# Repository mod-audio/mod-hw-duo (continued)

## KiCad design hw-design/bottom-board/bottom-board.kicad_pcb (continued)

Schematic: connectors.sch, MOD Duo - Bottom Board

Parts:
C55, C57: 100nF; C_0603_1608Metric; MPN C1608X7R1E104K080AA
C56: 10uF; CP_Elec_5x5.3; MPN UWX1E100MCL1GB
J1, J2, J3, J4, J5: JACK_TRS_6PINS; Jack_3.5mm_Neutrik_NMJ6HCD2_Horizontal; MPN NMJ6HCD2
J6: RJ45_LEDS; RJ45_Amphenol_RJHSE538X; MPN RJHSE-5381
P5: BARREL_JACK; BarrelJack_Horizontal; MPN PJ-002AH
P6: HMI_POWER; B2B-XH-A; MPN B2B-XH-A(LF)(SN)
P8: HMI_DATA; Pin_Header_Straight_2x10_Shrouded; MPN SBH11-PBPC-D10-ST-BK
P9: SERIAL_DEBUG; PinHeader_1x03_P2.54mm_Vertical
R72, R73: 100R; R_0603_1608Metric; MPN RMCF0603JT100R
R76, R77: 330R; R_0603_1608Metric; MPN RMCF0603JT330R

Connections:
+12V: C56.1, C57.1, J6.4, J6.5, P6.2; also elsewhere on the board
CLI_UART_RX: P9.2, R73.2; also elsewhere on the board
CLI_UART_TX: P9.1, R72.2; also elsewhere on the board
GNDA: C55.2, C56.2, C57.2, J1.R, J1.S, J1.TN, J2.R, J2.S, J2.TN, J3.S, J4.S, J5.S, J6.7, J6.8, J6.9, J6.11, P5.2, P5.3, P6.1, P8.2, P8.5, P8.11, P8.12, P9.3; also elsewhere on the board
HMI_ISP_ENABLE: P8.14; also elsewhere on the board
HMI_RESET: P8.16; also elsewhere on the board
HMI_RFU_01(RX): P8.1; also elsewhere on the board
HMI_RFU_02(TX): P8.3; also elsewhere on the board
HMI_SPI0_CLK: P8.8; also elsewhere on the board
HMI_SPI0_CS0: P8.10; also elsewhere on the board
HMI_SPI0_MISO: P8.4; also elsewhere on the board
HMI_SPI0_MOSI: P8.6; also elsewhere on the board
HMI_UART_RX: P8.20; also elsewhere on the board
HMI_UART_TX: P8.18; also elsewhere on the board
HP_LEFT: J5.T; also elsewhere on the board
HP_RIGHT: J5.R; also elsewhere on the board
LEFT_AUDIO_INPUT: J1.T; also elsewhere on the board
LEFT_AUDIO_OUTPUT_RING: J3.R; also elsewhere on the board
LEFT_AUDIO_OUTPUT_TIP: J3.T; also elsewhere on the board
unnamed: J6.10, R77.1
unnamed: J6.12, R76.1
unnamed: P8.7, R72.1
unnamed: P8.9, R73.1
PM_LEDS_OE: P8.15; also elsewhere on the board
POWER_BUTTON: P8.13; also elsewhere on the board
POWER_INPUT: C55.1, P5.1; also elsewhere on the board
RIGHT_AUDIO_INPUT: J2.T; also elsewhere on the board
RIGHT_AUDIO_OUTPUT_RING: J4.R; also elsewhere on the board
RIGHT_AUDIO_OUTPUT_TIP: J4.T; also elsewhere on the board
RS485_RX+: J6.3; also elsewhere on the board
RS485_RX-: J6.6; also elsewhere on the board
RS485_RX_LED: R76.2; also elsewhere on the board
RS485_TX+: J6.1; also elsewhere on the board
RS485_TX-: J6.2; also elsewhere on the board
RS485_TX_LED: R77.2; also elsewhere on the board
TWI4_SCL: P8.17; also elsewhere on the board
TWI4_SDA: P8.19; also elsewhere on the board

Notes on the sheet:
POWER
AUDIO
CONTROL CHAIN
HMI

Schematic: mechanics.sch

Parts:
FID1, FID2, FID3: FIDUCIAL; fiducial_in-circuit
H1, H2, H3, H4, H5: HOLE; Hole_3.5mm

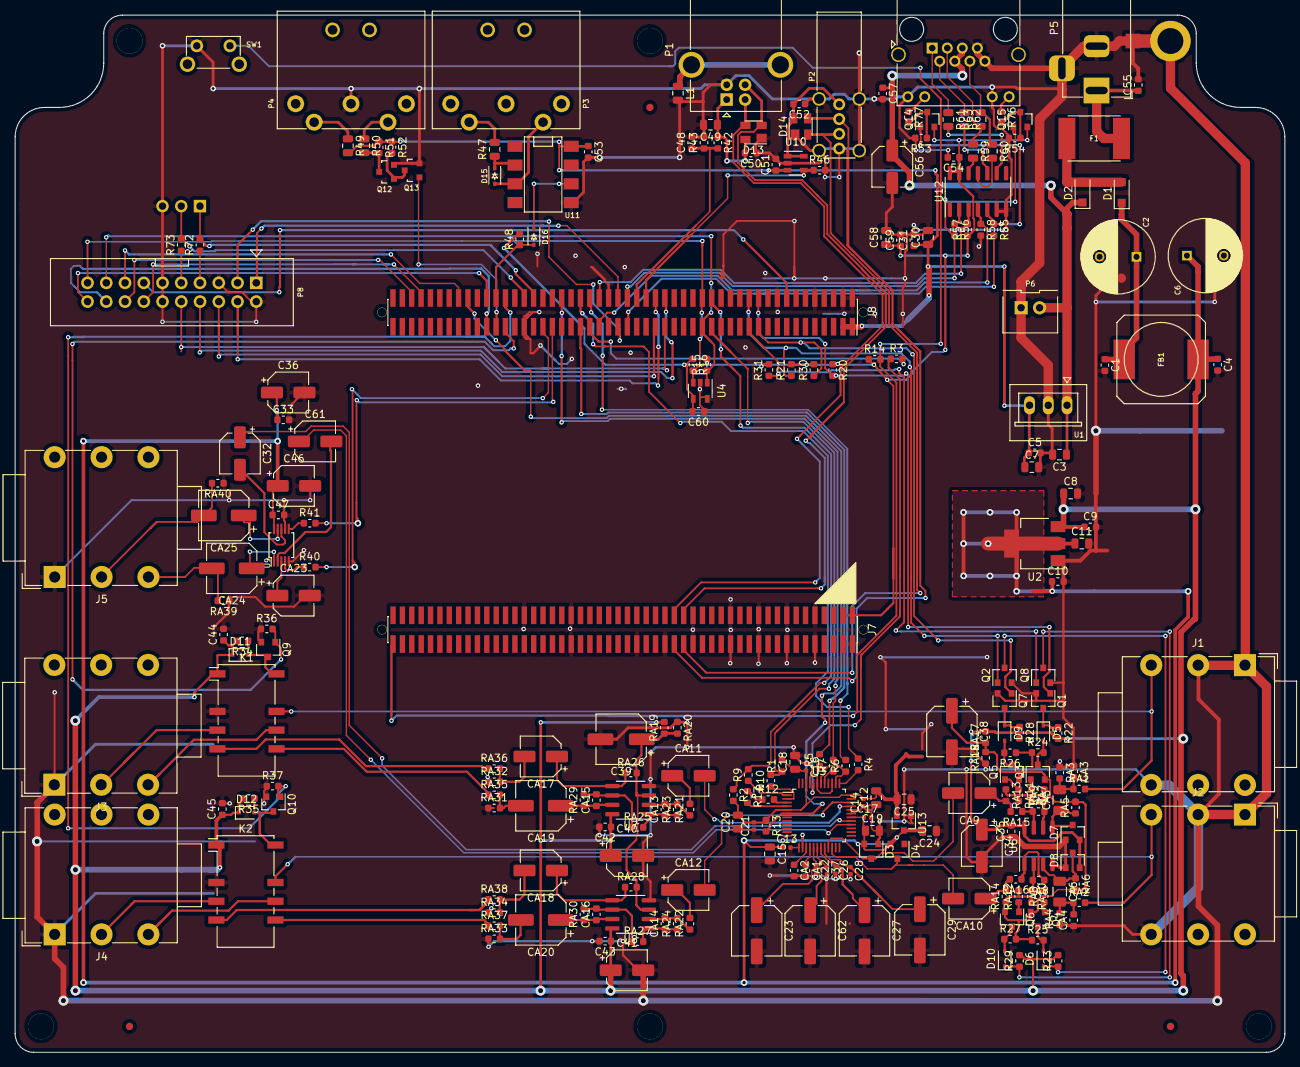
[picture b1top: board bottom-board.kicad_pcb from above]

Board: 2 copper layers, 172.0 x 140.5 mm, 255 parts (1 on the bottom side), 166 nets.

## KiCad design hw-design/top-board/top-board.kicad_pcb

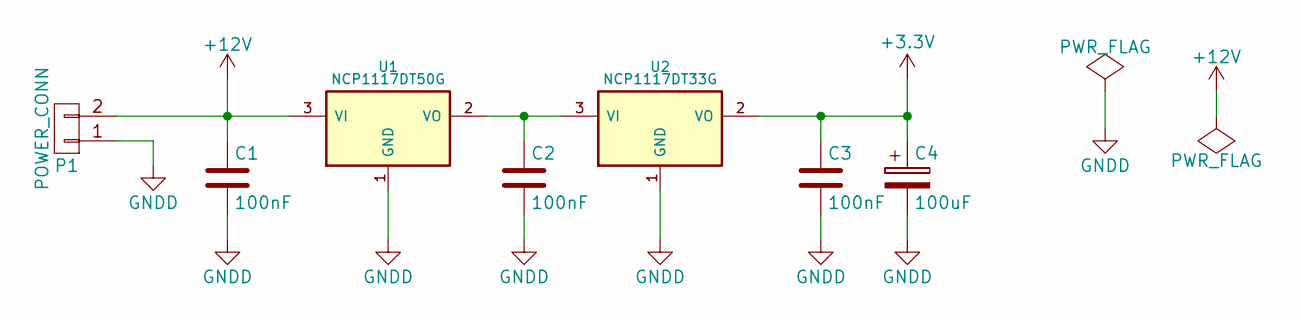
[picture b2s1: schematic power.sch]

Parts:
C1, C2, C3: 100nF; C_0603; MPN C1608X7R1E104K080AA
C4: 100uF; c_elec_6.3x5.3; MPN UWX1C101MCL1GB
P1: POWER_CONN; S2B-XH-A; MPN S2B-XH-A(LF)(SN)
U1: NCP1117DT50G; DPAK-2; MPN NCP1117DT50G
U2: NCP1117DT33G; DPAK-2; MPN NCP1117DT33G

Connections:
+3V3: C3.1, C4.1, U2.2 (VO); also elsewhere on the board
+12V: C1.1, P1.2, U1.3 (VI); also elsewhere on the board
GNDD: C1.2, C2.2, C3.2, C4.2, P1.1, U1.1 (GND), U2.1 (GND); also elsewhere on the board
unnamed: C2.1, U1.2 (VO), U2.3 (VI)

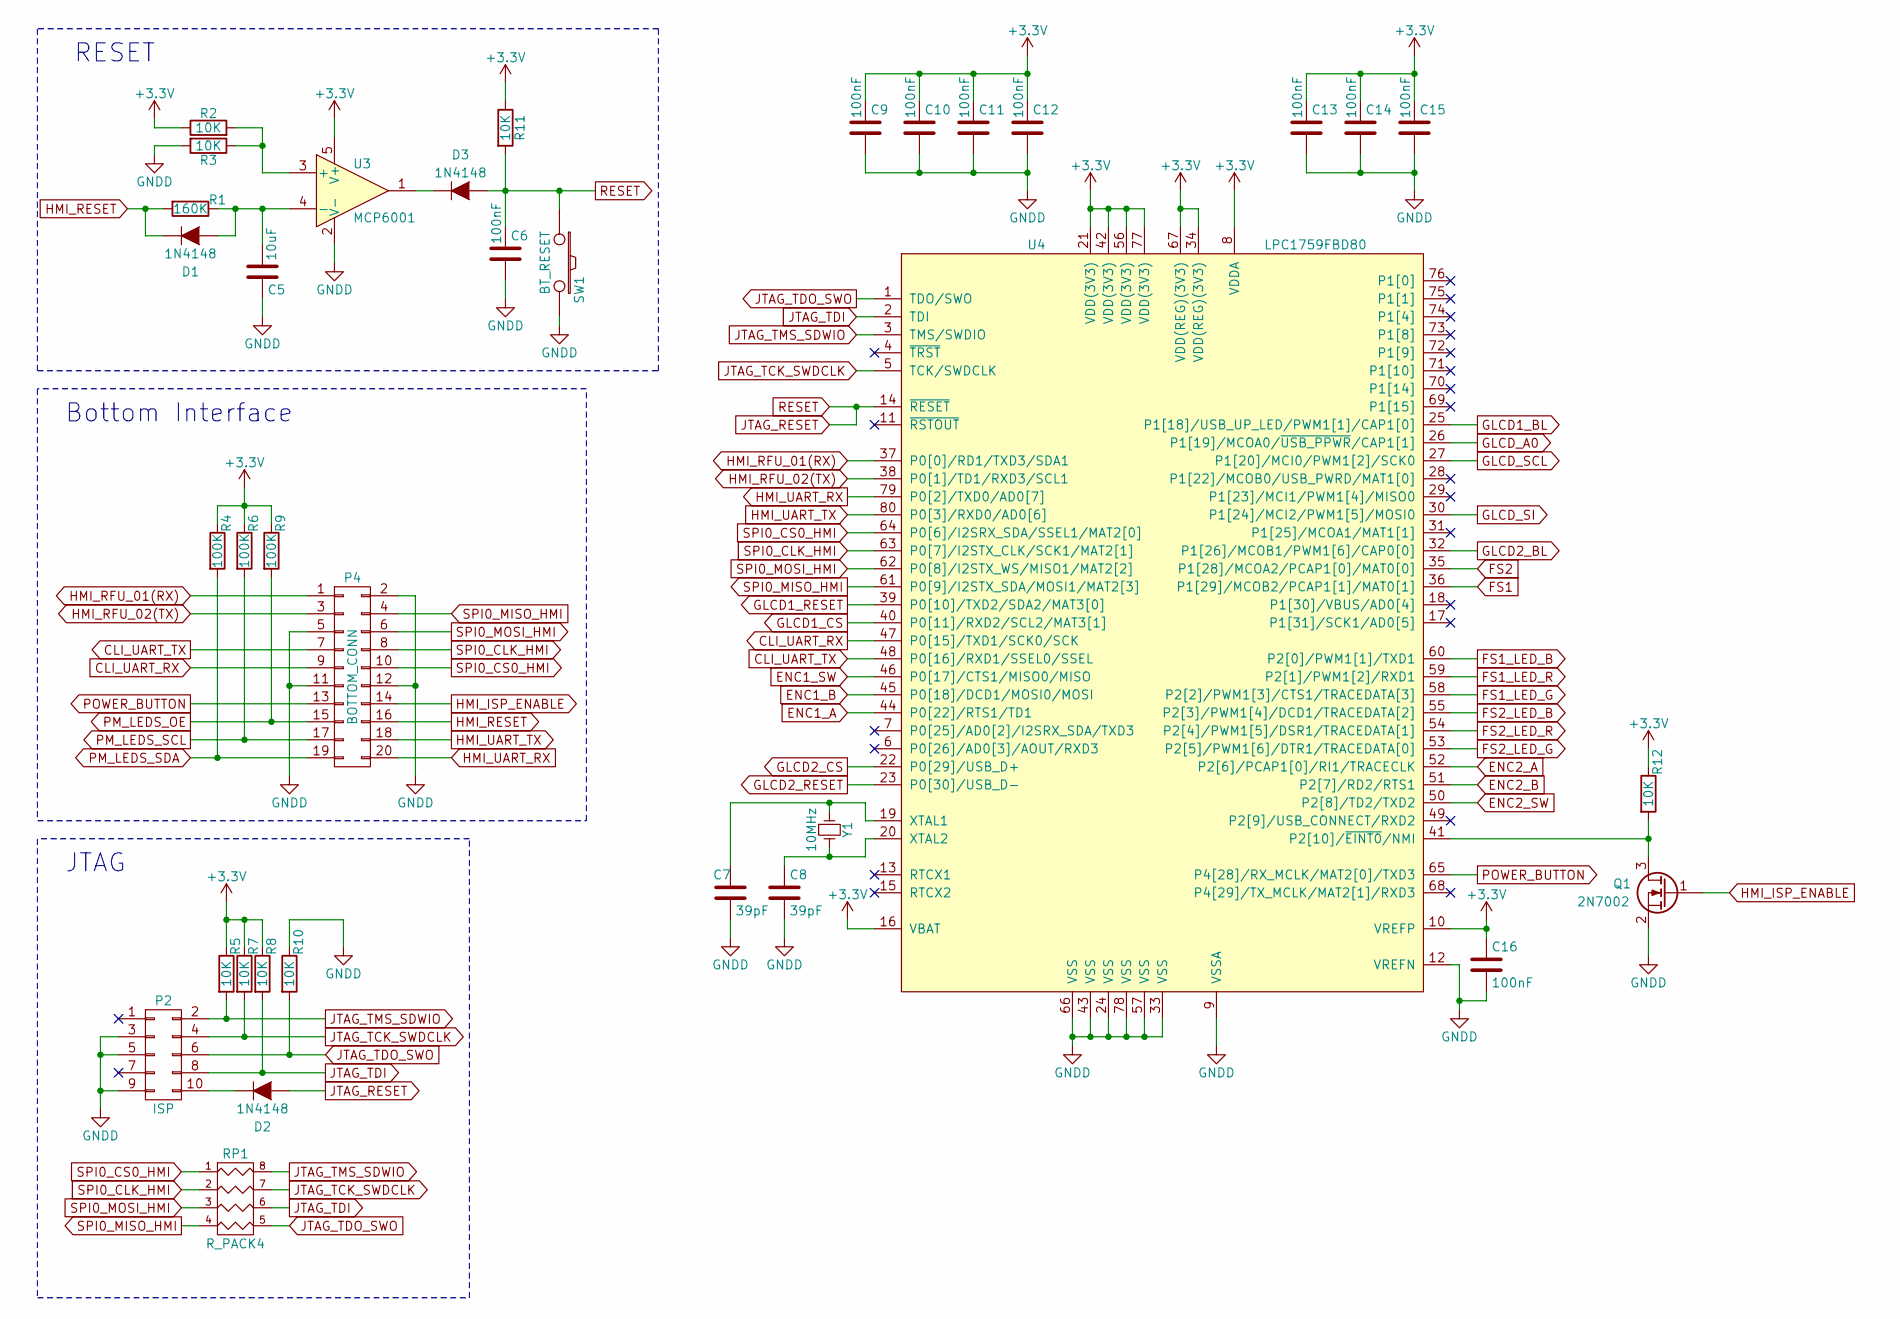
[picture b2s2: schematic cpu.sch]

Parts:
C5: 10uF; C_0805; MPN GRM219R61E106KA12D
C6, C9, C10, C11, C12, C13, C14, C15, C16: 100nF; C_0603; MPN C1608X7R1E104K080AA
C7, C8: 39pF; C_0603; MPN C1608C0G1H390J080AA
D1, D2, D3: 1N4148; SOD-323; MPN 1N4148WX-TP
P2: ISP; Pin_Header_Straight_2x05_Pitch1.27mm
P4: BOTTOM_CONN; Pin_Header_Angled_2x10; MPN 68021-220HLF
Q1: 2N7002; SOT-23; MPN 2N7002P,215
R1: 160K; R_0603; MPN RMCF0603JT160K
R2, R3, R5, R7, R8, R10, R11, R12: 10K; R_0603; MPN RMCF0603JT10K0
R4, R6, R9: 100K; R_0603; MPN RMCF0603JT100K
RP1: R_PACK4; R_Array_Concave_4x0402
SW1: BT_RESET; SW_SPST_FSMSM; MPN FSMSM
U3: MCP6001; SOT-23-5; MPN MCP6001T-I/OT
U4: LPC1759FBD80; LQFP-80_12x12mm_Pitch0.5mm; MPN LPC1759FBD80,551
Y1: 10MHz; Crystal_HC49-SD_SMD; MPN FOXSDLF/100-20

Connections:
+3V3: C9.1, C10.1, C11.1, C12.1, C13.1, C14.1, C15.1, C16.1, R2.1, R4.1, R5.1, R6.1, R7.1, R8.1, R9.1, R11.1, R12.1, U3.5 (V+), U4.8 (VDDA), U4.10 (VREFP), U4.16 (VBAT), U4.21 (VDD(3V3)), U4.34 (VDD(REG)(3V3)), U4.42 (VDD(3V3)), U4.56 (VDD(3V3)), U4.67 (VDD(REG)(3V3)), U4.77 (VDD(3V3)); also elsewhere on the board
CLI_UART_RX: P4.9, U4.47 (P0[15]/TXD1/SCK0/SCK)
CLI_UART_TX: P4.7, U4.48 (P0[16]/RXD1/SSEL0/SSEL)
ENC1_A: U4.44 (P0[22]/RTS1/TD1); also elsewhere on the board
ENC1_B: U4.45 (P0[18]/DCD1/MOSI0/MOSI); also elsewhere on the board
ENC1_SW: U4.46 (P0[17]/CTS1/MISO0/MISO); also elsewhere on the board
ENC2_A: U4.52 (P2[6]/PCAP1[0]/RI1/TRACECLK); also elsewhere on the board
ENC2_B: U4.51 (P2[7]/RD2/RTS1); also elsewhere on the board
ENC2_SW: U4.50 (P2[8]/TD2/TXD2); also elsewhere on the board
FS1: U4.36 (P1[29]/MCOB2/PCAP1[1]/MAT0[1]); also elsewhere on the board
FS1_LED_B: U4.60 (P2[0]/PWM1[1]/TXD1); also elsewhere on the board
FS1_LED_G: U4.58 (P2[2]/PWM1[3]/CTS1/TRACEDATA[3]); also elsewhere on the board
FS1_LED_R: U4.59 (P2[1]/PWM1[2]/RXD1); also elsewhere on the board
FS2: U4.35 (P1[28]/MCOA2/PCAP1[0]/MAT0[0]); also elsewhere on the board
FS2_LED_B: U4.55 (P2[3]/PWM1[4]/DCD1/TRACEDATA[2]); also elsewhere on the board
FS2_LED_G: U4.53 (P2[5]/PWM1[6]/DTR1/TRACEDATA[0]); also elsewhere on the board
FS2_LED_R: U4.54 (P2[4]/PWM1[5]/DSR1/TRACEDATA[1]); also elsewhere on the board
GLCD1_BL: U4.25 (P1[18]/USB_UP_LED/PWM1[1]/CAP1[0]); also elsewhere on the board
GLCD1_CS: U4.40 (P0[11]/RXD2/SCL2/MAT3[1]); also elsewhere on the board
GLCD1_RESET: U4.39 (P0[10]/TXD2/SDA2/MAT3[0]); also elsewhere on the board
GLCD2_BL: U4.32 (P1[26]/MCOB1/PWM1[6]/CAP0[0]); also elsewhere on the board
GLCD2_CS: U4.22 (P0[29]/USB_D+); also elsewhere on the board
GLCD2_RESET: U4.23 (P0[30]/USB_D-); also elsewhere on the board
GLCD_A0: U4.26 (P1[19]/MCOA0/~USB_PPWR~/CAP1[1]); also elsewhere on the board
GLCD_SCL: U4.27 (P1[20]/MCI0/PWM1[2]/SCK0); also elsewhere on the board
GLCD_SI: U4.30 (P1[24]/MCI2/PWM1[5]/MOSI0); also elsewhere on the board
GNDD: C5.1, C6.2, C7.2, C8.2, C9.2, C10.2, C11.2, C12.2, C13.2, C14.2, C15.2, C16.2, P2.3, P2.5, P2.9, P4.2, P4.5, P4.11, P4.12, Q1.2 (S), R3.2, R10.1, SW1.2, U3.2 (V-), U4.9 (VSSA), U4.12 (VREFN), U4.24 (VSS), U4.33 (VSS), U4.43 (VSS), U4.57 (VSS), U4.66 (VSS), U4.78 (VSS); also elsewhere on the board
HMI_ISP_ENABLE: P4.14, Q1.1 (G)
HMI_RESET: D1.1 (K), P4.16, R1.2
HMI_RFU_01(RX): P4.1, U4.37 (P0[0]/RD1/TXD3/SDA1)
HMI_RFU_02(TX): P4.3, U4.38 (P0[1]/TD1/RXD3/SCL1)
HMI_UART_RX: P4.20, U4.79 (P0[2]/TXD0/AD0[7])
HMI_UART_TX: P4.18, U4.80 (P0[3]/RXD0/AD0[6])
JTAG_RESET: C6.1, D2.2 (A), D3.2 (A), R11.2, SW1.1, U4.14 (~RESET~)
JTAG_TCK_SWDCLK: P2.4, R7.2, RP1.7 (R2), U4.5 (TCK/SWDCLK)
JTAG_TDI: P2.8, R8.2, RP1.6 (R3), U4.2 (TDI)
JTAG_TDO_SWO: P2.6, R10.2, RP1.5 (R4), U4.1 (TDO/SWO)
JTAG_TMS_SDWIO: P2.2, R5.2, RP1.8 (R1), U4.3 (TMS/SWDIO)
unnamed: C5.2, D1.2 (A), R1.1, U3.4 (-)
unnamed: C7.1, U4.19 (XTAL1), Y1.1
unnamed: C8.1, U4.20 (XTAL2), Y1.2
unnamed: D2.1 (K), P2.10
unnamed: D3.1 (K), U3.1
unnamed: Q1.3 (D), R12.2, U4.41 (P2[10]/~EINT0~/NMI)
unnamed: R2.2, R3.1, U3.3 (+)
PM_LEDS_OE: P4.15, R9.2; also elsewhere on the board
PM_LEDS_SCL: P4.17, R6.2; also elsewhere on the board
PM_LEDS_SDA: P4.19, R4.2; also elsewhere on the board
POWER_BUTTON: P4.13, U4.65 (P4[28]/RX_MCLK/MAT2[0]/TXD3)
SPI0_CLK_HMI: P4.8, RP1.2, U4.63 (P0[7]/I2STX_CLK/SCK1/MAT2[1])
SPI0_CS0_HMI: P4.10, RP1.1, U4.64 (P0[6]/I2SRX_SDA/SSEL1/MAT2[0])
SPI0_MISO_HMI: P4.4, RP1.4, U4.61 (P0[9]/I2STX_SDA/MOSI1/MAT2[3])
SPI0_MOSI_HMI: P4.6, RP1.3, U4.62 (P0[8]/I2STX_WS/MISO1/MAT2[2])

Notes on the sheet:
JTAG
Bottom Interface
RESET

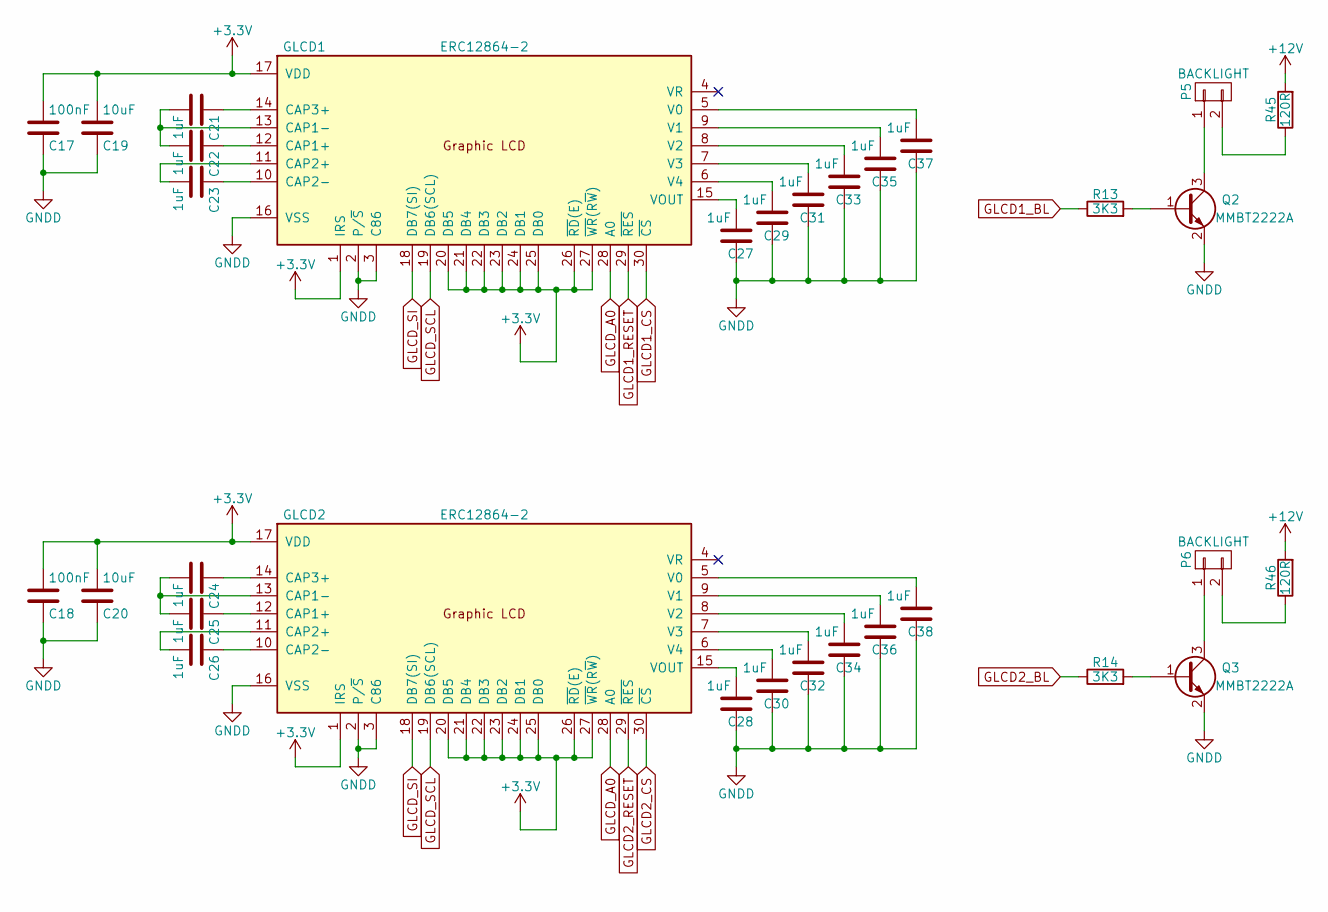
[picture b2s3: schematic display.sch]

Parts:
C17, C18: 100nF; C_0603; MPN C1608X7R1E104K080AA
C19, C20: 10uF; C_0805; MPN GRM219R61E106KA12D
C21, C22, C23, C24, C25, C26, C27, C28, C29, C30, C31, C32, C33, C34, C35, C36, C37, C38: 1uF; C_0805; MPN C2012X7R1E105K125AB
GLCD1, GLCD2: ERC12864-2; ER-CON30HB-1; MPN ER-CON30HT-1
P5, P6: BACKLIGHT; SMD_Pin_Header_Angled_2x01_Pitch2.00mm; MPN ER-CON2.0-2P-SMD
Q2, Q3: MMBT2222A; SOT-23; MPN MMBT2222ALT1G
R13, R14: 3K3; R_0603; MPN RMCF0603JT3K30
R45, R46: 120R; R_2512; MPN 2-2176070-7

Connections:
+3V3: C17.2, C18.2, C19.2, C20.2, GLCD1.1 (IRS), GLCD1.17 (VDD), GLCD1.20 (DB5), GLCD1.21 (DB4), GLCD1.22 (DB3), GLCD1.23 (DB2), GLCD1.24 (DB1), GLCD1.25 (DB0), GLCD1.26 (~RD~(E)), GLCD1.27 (~WR~(R~W~)), GLCD2.1 (IRS), GLCD2.17 (VDD), GLCD2.20 (DB5), GLCD2.21 (DB4), GLCD2.22 (DB3), GLCD2.23 (DB2), GLCD2.24 (DB1), GLCD2.25 (DB0), GLCD2.26 (~RD~(E)), GLCD2.27 (~WR~(R~W~)); also elsewhere on the board
+12V: R45.2, R46.2; also elsewhere on the board
GLCD1_BL: R13.1; also elsewhere on the board
GLCD1_CS: GLCD1.30 (~CS~); also elsewhere on the board
GLCD1_RESET: GLCD1.29 (~RES~); also elsewhere on the board
GLCD2_BL: R14.1; also elsewhere on the board
GLCD2_CS: GLCD2.30 (~CS~); also elsewhere on the board
GLCD2_RESET: GLCD2.29 (~RES~); also elsewhere on the board
GLCD_A0: GLCD1.28 (A0), GLCD2.28 (A0); also elsewhere on the board
GLCD_SCL: GLCD1.19 (DB6(SCL)), GLCD2.19 (DB6(SCL)); also elsewhere on the board
GLCD_SI: GLCD1.18 (DB7(SI)), GLCD2.18 (DB7(SI)); also elsewhere on the board
GNDD: C17.1, C18.1, C19.1, C20.1, C27.1, C28.1, C29.1, C30.1, C31.1, C32.1, C33.1, C34.1, C35.1, C36.1, C37.1, C38.1, GLCD1.2 (P/~S~), GLCD1.3 (C86), GLCD1.16 (VSS), GLCD2.2 (P/~S~), GLCD2.3 (C86), GLCD2.16 (VSS), Q2.2 (E), Q3.2 (E); also elsewhere on the board
unnamed: C21.1, GLCD1.14 (CAP3+)
unnamed: C21.2, C22.2, GLCD1.13 (CAP1-)
unnamed: C22.1, GLCD1.12 (CAP1+)
unnamed: C23.1, GLCD1.10 (CAP2-)
unnamed: C23.2, GLCD1.11 (CAP2+)
unnamed: C24.1, GLCD2.14 (CAP3+)
unnamed: C24.2, C25.2, GLCD2.13 (CAP1-)
unnamed: C25.1, GLCD2.12 (CAP1+)
unnamed: C26.1, GLCD2.10 (CAP2-)
unnamed: C26.2, GLCD2.11 (CAP2+)
unnamed: C27.2, GLCD1.15 (VOUT)
unnamed: C28.2, GLCD2.15 (VOUT)
unnamed: C29.2, GLCD1.6 (V4)
unnamed: C30.2, GLCD2.6 (V4)
unnamed: C31.2, GLCD1.7 (V3)
unnamed: C32.2, GLCD2.7 (V3)
unnamed: C33.2, GLCD1.8 (V2)
unnamed: C34.2, GLCD2.8 (V2)
unnamed: C35.2, GLCD1.9 (V1)
unnamed: C36.2, GLCD2.9 (V1)
unnamed: C37.2, GLCD1.5 (V0)
unnamed: C38.2, GLCD2.5 (V0)
unnamed: P5.1, Q2.3 (C)
unnamed: P5.2, R45.1
unnamed: P6.1, Q3.3 (C)
unnamed: P6.2, R46.1
unnamed: Q2.1 (B), R13.2
unnamed: Q3.1 (B), R14.2

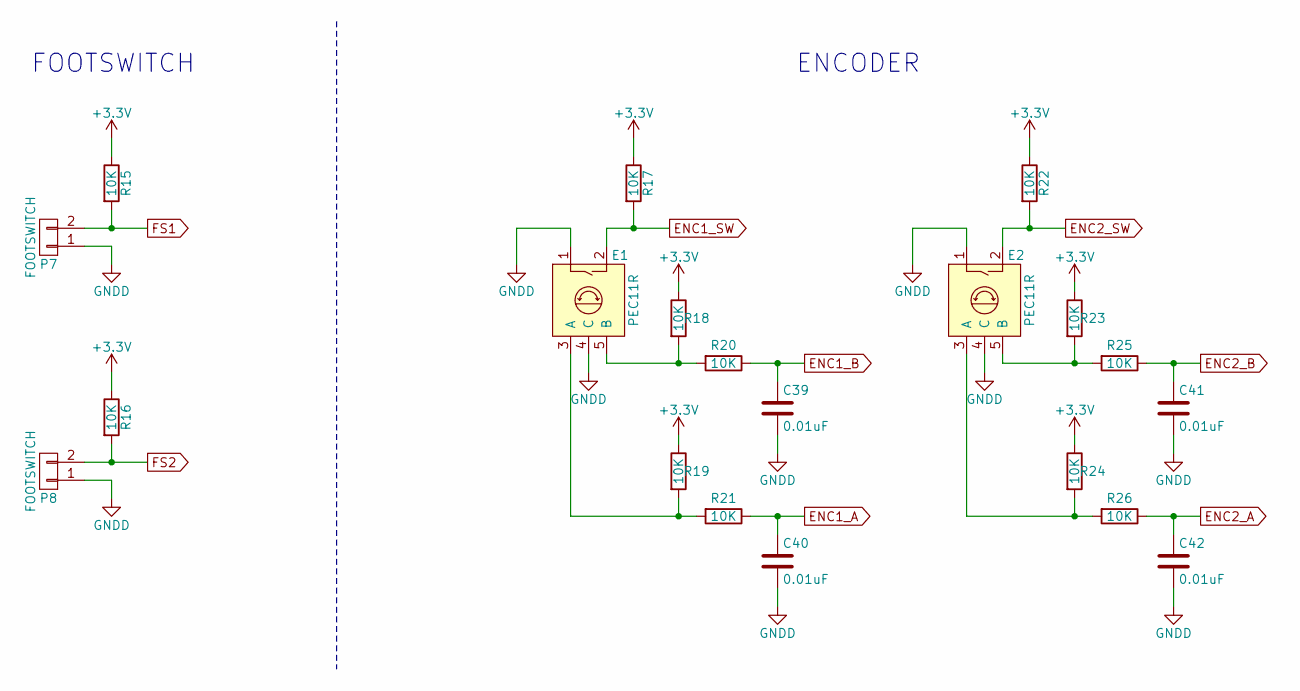
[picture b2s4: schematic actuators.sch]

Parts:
C39, C40, C41, C42: 0.01uF; C_0603; MPN C1608X7R1E103K080AA
E1, E2: PEC11R; PEC11R-4xxxF-Sxxxx; MPN PEC11R-4020F-S0024
P7, P8: FOOTSWITCH; Pin_Header_Angled_1x02; MPN M20-9960245
R15, R16, R17, R18, R19, R20, R21, R22, R23, R24, R25, R26: 10K; R_0603; MPN RMCF0603JT10K0

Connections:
+3V3: R15.1, R16.1, R17.1, R18.1, R19.1, R22.1, R23.1, R24.1; also elsewhere on the board
ENC1_A: C40.1, R21.1; also elsewhere on the board
ENC1_B: C39.1, R20.1; also elsewhere on the board
ENC1_SW: E1.2, R17.2; also elsewhere on the board
ENC2_A: C42.1, R26.1; also elsewhere on the board
ENC2_B: C41.1, R25.1; also elsewhere on the board
ENC2_SW: E2.2, R22.2; also elsewhere on the board
FS1: P7.2, R15.2; also elsewhere on the board
FS2: P8.2, R16.2; also elsewhere on the board
GNDD: C39.2, C40.2, C41.2, C42.2, E1.1, E1.4 (C), E2.1, E2.4 (C), P7.1, P8.1; also elsewhere on the board
unnamed: E1.3 (A), R19.2, R21.2
unnamed: E1.5 (B), R18.2, R20.2
unnamed: E2.3 (A), R24.2, R26.2
unnamed: E2.5 (B), R23.2, R25.2

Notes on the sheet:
FOOTSWITCH
ENCODER

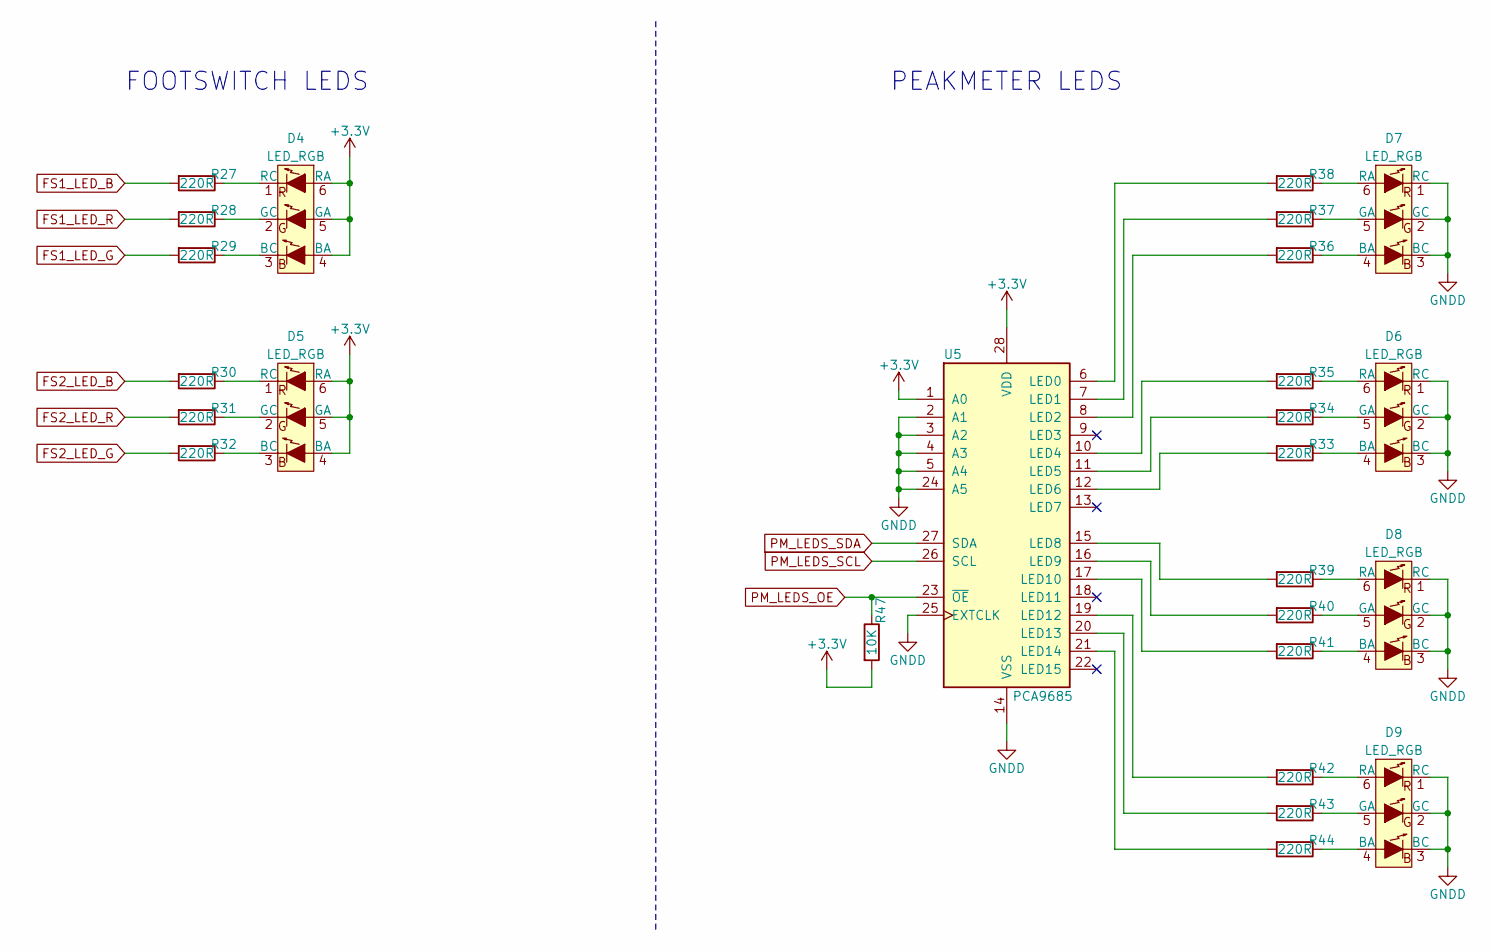
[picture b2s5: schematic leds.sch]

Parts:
D4, D5, D6, D7, D8, D9: LED_RGB; LED_RGB_PLLC-6; MPN LTRBGFSF-ABCB-QKYO-Z
R27, R28, R29, R30, R31, R32, R33, R34, R35, R36, R37, R38, R39, R40, R41, R42, R43, R44: 220R; R_0603; MPN RMCF0603JT220R
R47: 10K; R_0603; MPN RMCF0603JT10K0
U5: PCA9685; TSSOP-28_4.4x9.7mm_Pitch0.65mm; MPN PCA9685PW,118

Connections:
+3V3: D4.4 (BA), D4.5 (GA), D4.6 (RA), D5.4 (BA), D5.5 (GA), D5.6 (RA), R47.2, U5.1 (A0), U5.28 (VDD); also elsewhere on the board
FS1_LED_B: R27.2; also elsewhere on the board
FS1_LED_G: R29.2; also elsewhere on the board
FS1_LED_R: R28.2; also elsewhere on the board
FS2_LED_B: R30.2; also elsewhere on the board
FS2_LED_G: R32.2; also elsewhere on the board
FS2_LED_R: R31.2; also elsewhere on the board
GNDD: D6.1 (RC), D6.2 (GC), D6.3 (BC), D7.1 (RC), D7.2 (GC), D7.3 (BC), D8.1 (RC), D8.2 (GC), D8.3 (BC), D9.1 (RC), D9.2 (GC), D9.3 (BC), U5.2 (A1), U5.3 (A2), U5.4 (A3), U5.5 (A4), U5.14 (VSS), U5.24 (A5), U5.25 (EXTCLK); also elsewhere on the board
unnamed: D4.1 (RC), R27.1
unnamed: D4.2 (GC), R28.1
unnamed: D4.3 (BC), R29.1
unnamed: D5.1 (RC), R30.1
unnamed: D5.2 (GC), R31.1
unnamed: D5.3 (BC), R32.1
unnamed: D6.4 (BA), R33.1
unnamed: D6.5 (GA), R34.1
unnamed: D6.6 (RA), R35.1
unnamed: D7.4 (BA), R36.1
unnamed: D7.5 (GA), R37.1
unnamed: D7.6 (RA), R38.1
unnamed: D8.4 (BA), R41.1
unnamed: D8.5 (GA), R40.1
unnamed: D8.6 (RA), R39.1
unnamed: D9.4 (BA), R44.1
unnamed: D9.5 (GA), R43.1
unnamed: D9.6 (RA), R42.1
unnamed: R33.2, U5.12 (LED6)
unnamed: R34.2, U5.11 (LED5)
unnamed: R35.2, U5.10 (LED4)
unnamed: R36.2, U5.8 (LED2)
unnamed: R37.2, U5.7 (LED1)
unnamed: R38.2, U5.6 (LED0)
unnamed: R39.2, U5.15 (LED8)
unnamed: R40.2, U5.16 (LED9)
unnamed: R41.2, U5.17 (LED10)
unnamed: R42.2, U5.19 (LED12)
unnamed: R43.2, U5.20 (LED13)
unnamed: R44.2, U5.21 (LED14)
PM_LEDS_OE: R47.1, U5.23 (~OE~); also elsewhere on the board
PM_LEDS_SCL: U5.26 (SCL); also elsewhere on the board
PM_LEDS_SDA: U5.27 (SDA); also elsewhere on the board

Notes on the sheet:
FOOTSWITCH LEDS
PEAKMETER LEDS

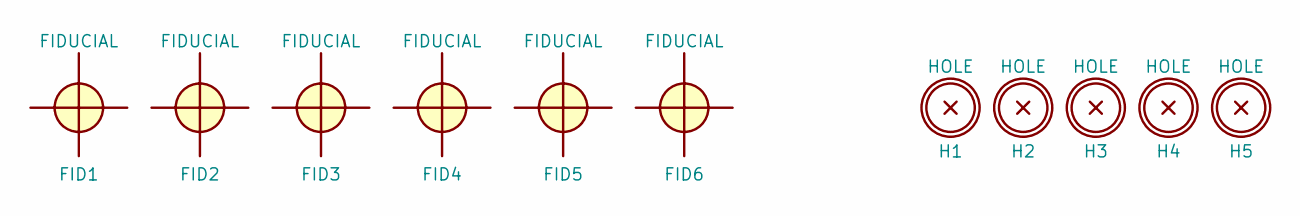
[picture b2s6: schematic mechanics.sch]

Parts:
FID1, FID2, FID3, FID4, FID5, FID6: FIDUCIAL; fiducial_in-circuit
H1, H2, H3, H4, H5: HOLE; Hole_3.5mm

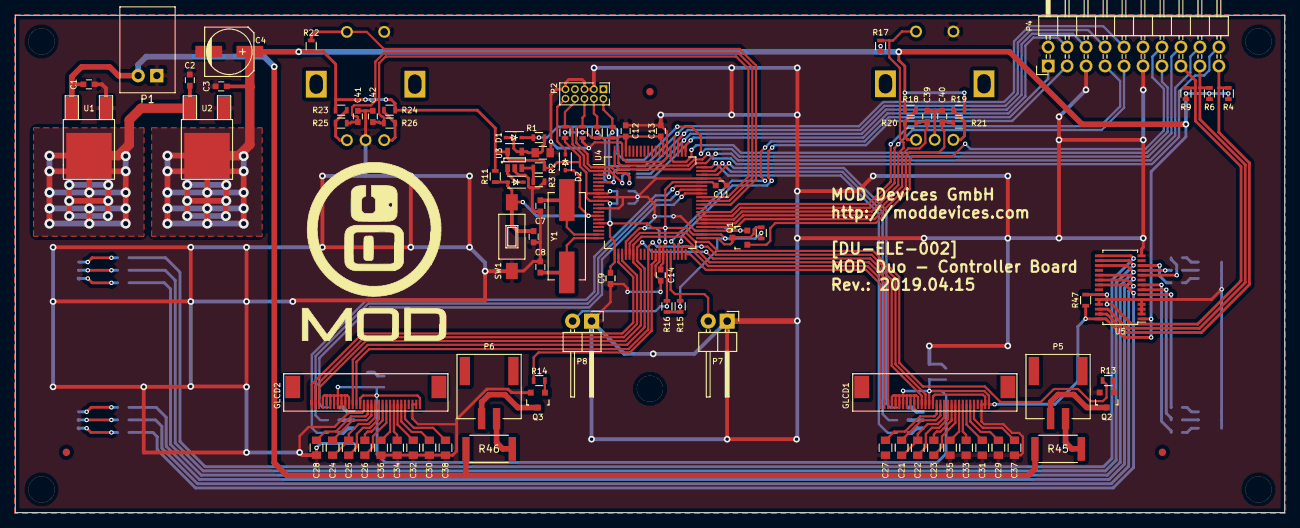
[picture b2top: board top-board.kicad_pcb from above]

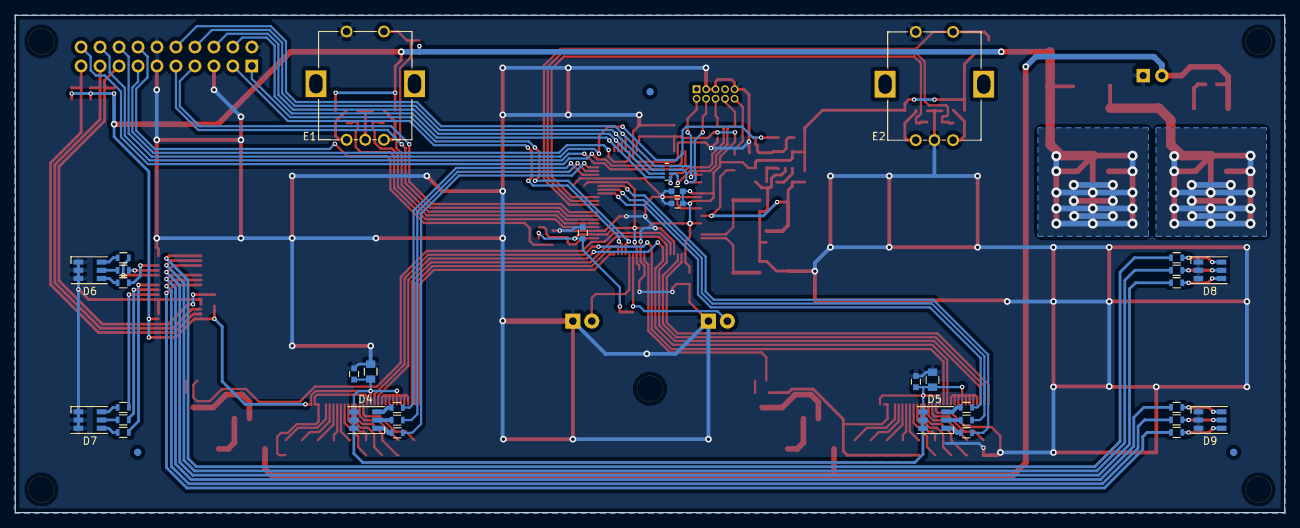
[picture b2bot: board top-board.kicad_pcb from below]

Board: 2 copper layers, 170.0 x 66.6 mm, 131 parts (37 on the bottom side), 117 nets.

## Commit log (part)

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2019-03-28 Changed SODIM to Marsboard header + added liniar regulator for audio codec
2019-03-29 improved routing
2019-04-15 Changed capacitor posistion & changed relay footprint
2019-04-15 added logo's and updated gerber files
2019-04-15 Changed U10 to another chip due to unavailability
2019-08-16 changed a bottomboard to a minimal HMI testing unit
2019-08-16 added final BOM files
2019-08-16 added PDF
2019-10-07 updated footprints and MPN's
2019-10-11 correct tracks that overlap with new footprints
2024-10-06 README: fix link to KiCAD homepage
